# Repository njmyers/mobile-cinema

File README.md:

## Description

Mobile cinema is an audio/visual presentation unit designed for the rough conditions of the field. It is a solar powered, efficient and durable system that can endure the hardships associated with transportation, inclement weather and outdoor conditions. It emphasizes power efficiency and usability over features to create a product that satisfies the use case as cleanly as possible.

The cinema uses a pre-fabricated case with custom electronic and physical parts. Physical parts are fabricated using 3D printing and 2D laser cutting. The materials used are PETG for printing and matte acrylic for 2D cut parts. The parts are then assembled using a combination of structural plastic adhesives and M3 hardware. Electronic parts include some store bought parts such as the TV and solar panel as well as custom circuit boards for routing and switching. All electronics are mounted using printed parts and wiring is done by hand.

The end result is a highly durable, flexible and efficient product that performs very well under harsh conditions and can be easily operated after a simple training session.

## BOM

Parts lists are located in this repository as well as the following [google sheet](https://docs.google.com/spreadsheets/d/1YABbkeHETHl9nhduOOJQ0aeivhLUgdqu8qCclFDEOm0/edit?usp=sharing).

## Photos

_Village Video v4.1 Product Photo_

_Village Video v4.1 Top View_

_Village Video v4.1 In Use_

## Links

- PVI International [Project Description](https://www.pvinternational.org/projects/kibanda-boda/)
- PVI International [v4.0 Release](https://www.pvinternational.org/news/pvi-launches-village-video-4-0/)

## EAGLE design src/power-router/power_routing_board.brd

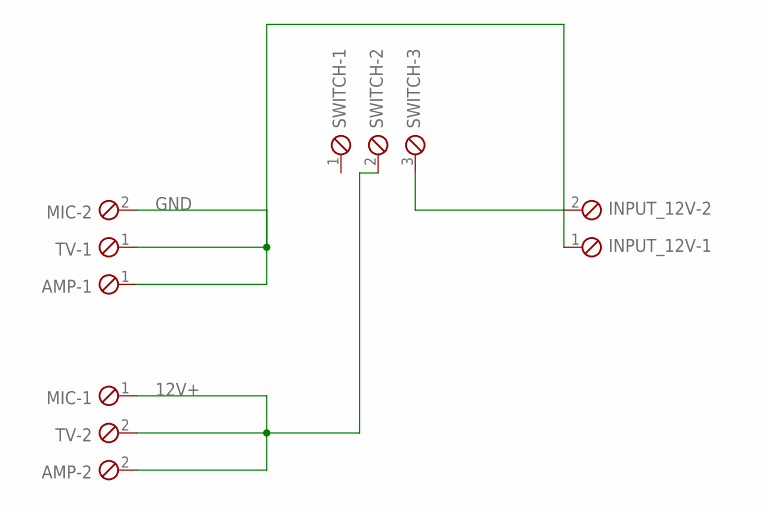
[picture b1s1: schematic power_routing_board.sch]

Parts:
AMP: TB3POL; 2POL381
INPUT_12V: TB3POL; 2POL381
MIC: TB3POL; 2POL381
SWITCH: TB3POL; 3POL381
TV: TB3POL; 2POL381

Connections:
12V+: AMP.2, MIC.1, SWITCH.2, TV.2
GND: AMP.1, INPUT_12V.1, MIC.2, TV.1
unnamed: INPUT_12V.2, SWITCH.3

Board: 2 copper layers, 5 parts (0 on the bottom side), 3 nets, no tracks yet.

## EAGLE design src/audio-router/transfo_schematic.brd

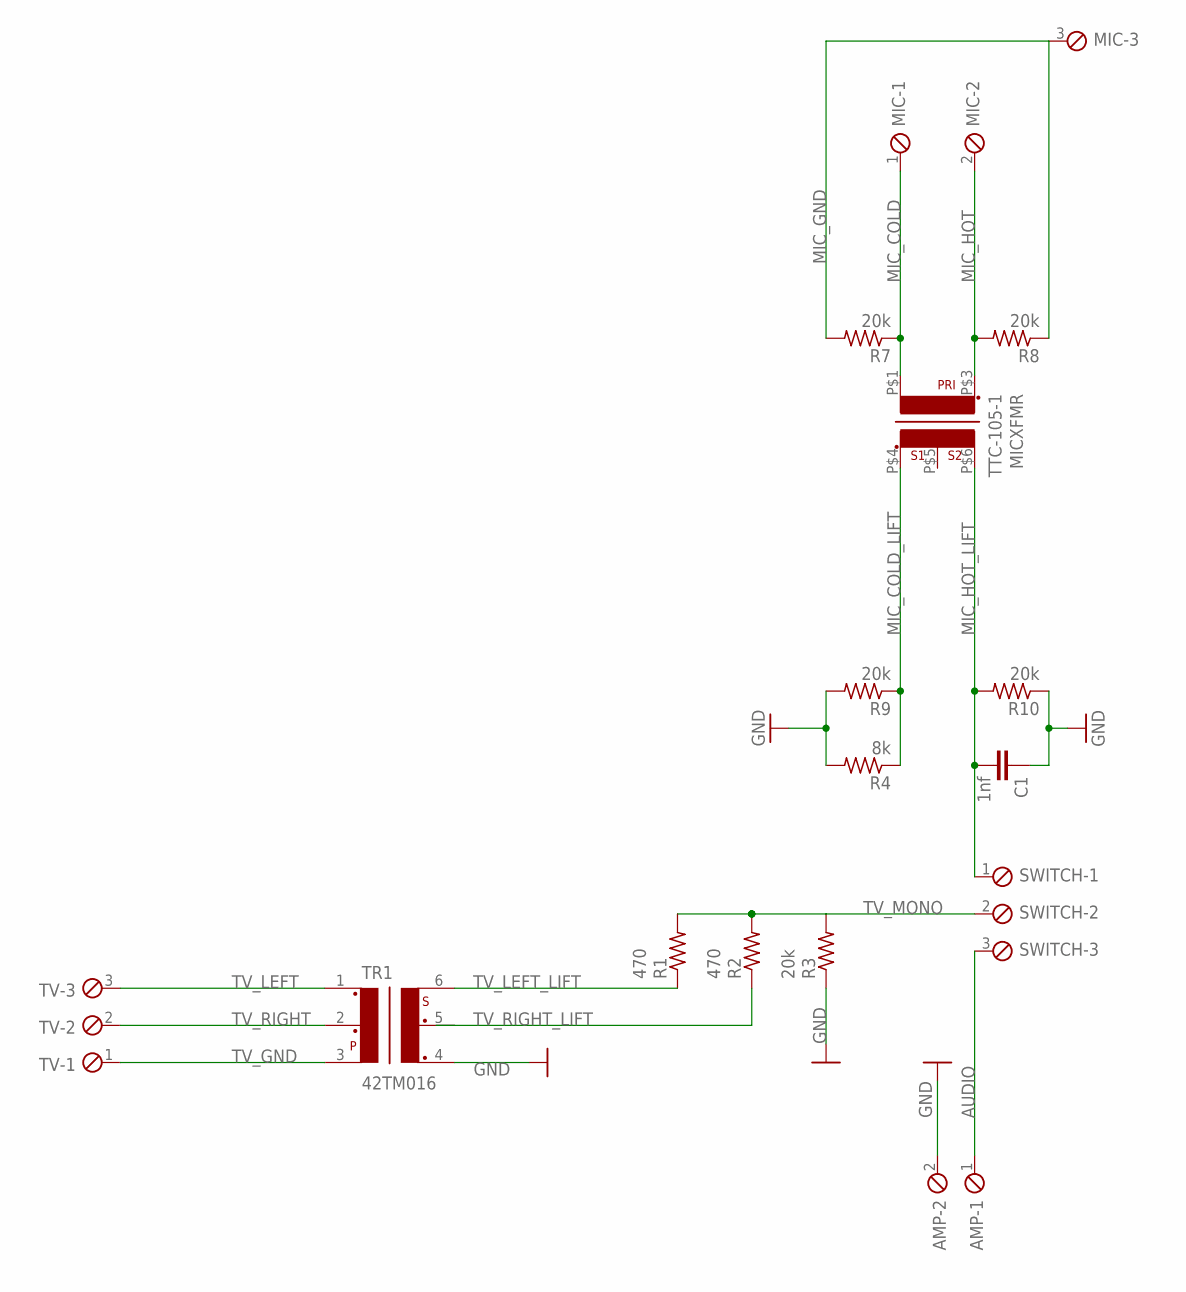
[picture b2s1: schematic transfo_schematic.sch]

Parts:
AMP: TB3POL; 2POL381
C1: 1nf; CAP-PTH-SMALL-KIT
MIC: TB3POL; 3POL381
MICXFMR: TTC-105-1; TAMURA-TTC-105-1
R1, R2: 470; 0204/7
R3, R7, R8, R9, R10: 20k; 0204/7
R4: 8k; 0204/7
SWITCH: TB3POL; 3POL381
TR1: 42TM016; 42TM
TV: TB3POL; 3POL381

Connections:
AUDIO: AMP.1, SWITCH.3
GND: AMP.2, C1.1, R3.1, R4.2, R9.2, R10.1, TR1.4
MIC_COLD: MIC.1, MICXFMR.P$1 (1), R7.1
MIC_COLD_LIFT: MICXFMR.P$4 (4), R4.1, R9.1
MIC_GND: MIC.3, R7.2, R8.1
MIC_HOT: MIC.2, MICXFMR.P$3 (3), R8.2
MIC_HOT_LIFT: C1.2, MICXFMR.P$6 (6), R10.2, SWITCH.1
TV_GND: TR1.3, TV.1
TV_LEFT: TR1.1, TV.3
TV_LEFT_LIFT: R1.1, TR1.6
TV_MONO: R1.2, R2.2, R3.2, SWITCH.2
TV_RIGHT: TR1.2, TV.2
TV_RIGHT_LIFT: R2.1, TR1.5

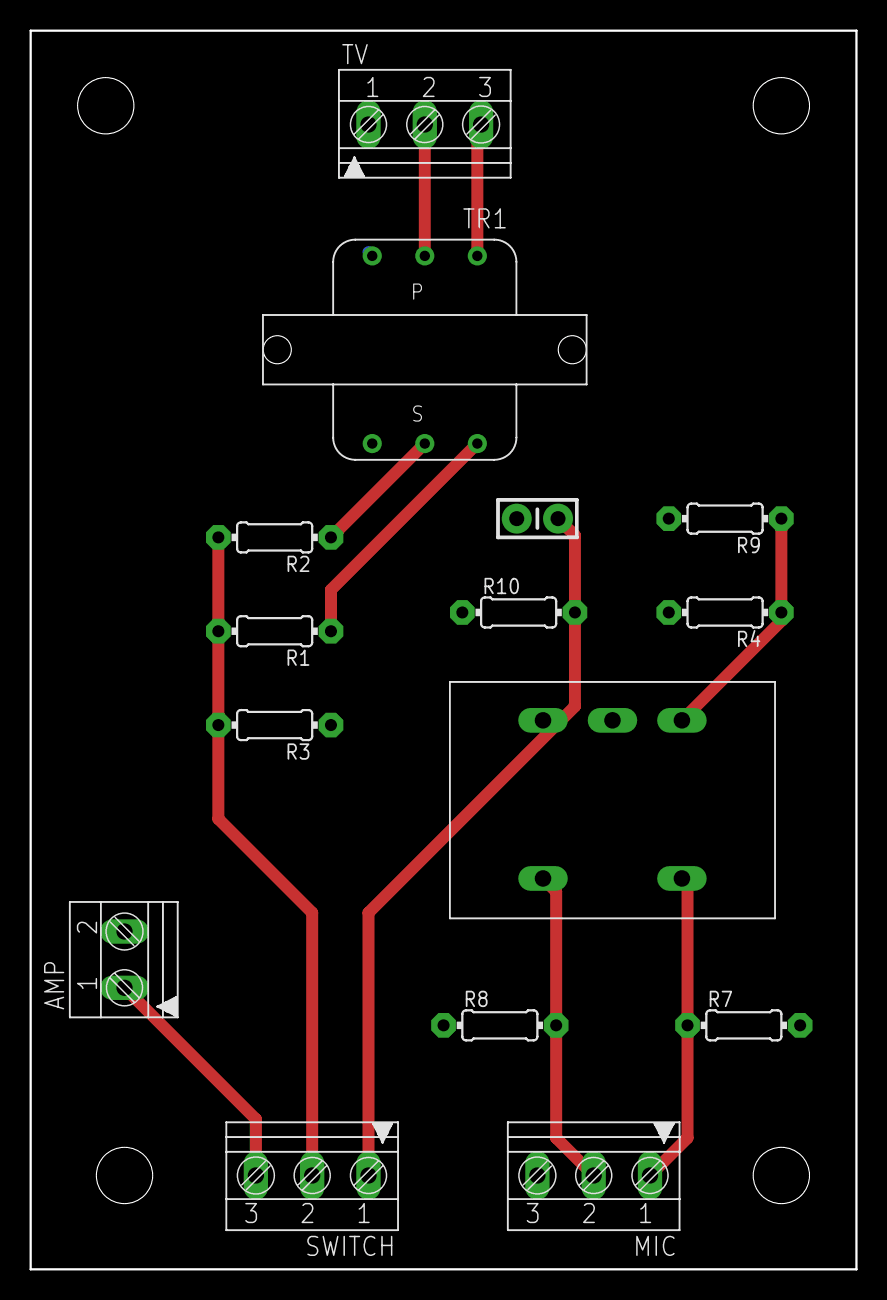
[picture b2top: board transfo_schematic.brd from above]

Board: 2 copper layers, 55.9 x 83.8 mm, 15 parts (0 on the bottom side), 13 nets.

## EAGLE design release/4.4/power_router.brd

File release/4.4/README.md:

### v4.4 Notes

This version has some great improvements. Most notable is the addition of a full depth bracket system for affixing the io panel, a power routing board, and fully transformer isolated audio inputs.

All boards now feature BOMs as well as an updated parts list for other commercially bought parts. Overall time to assemble a unit should be much less following these improvements.

### Changes

- Fixed terminal blocks for all connectors
- Transformer isolated audio inputs
- Full depth brackets for io board mounting
- Power routing board for easier assembly
- BOMs and parts lists
- Addition of TV spacer print file for different TV versions

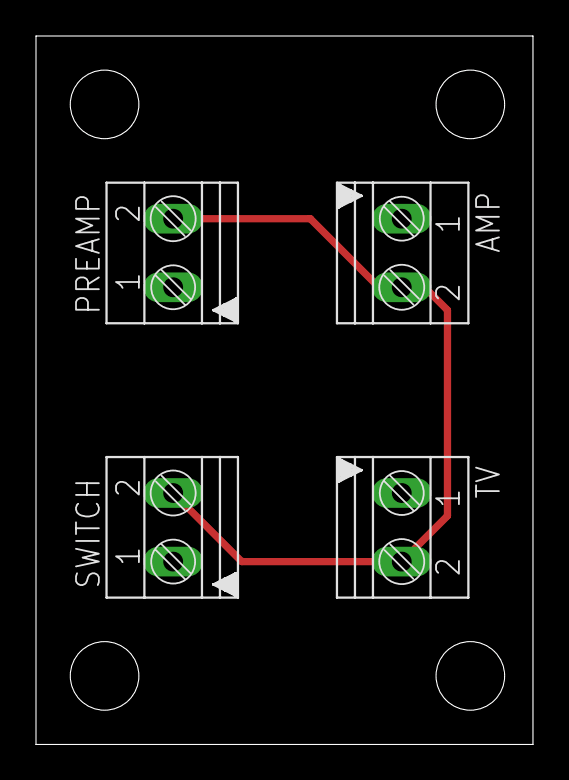
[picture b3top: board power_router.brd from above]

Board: 2 copper layers, 27.6 x 39.4 mm, 4 parts (0 on the bottom side), 2 nets.

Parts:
AMP: MKDS1/2-3,81; 2POL381
PREAMP: MKDS1/2-3,81; 2POL381
SWITCH: MKDS1/2-3,81; 2POL381
TV: MKDS1/2-3,81; 2POL381

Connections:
+12V: AMP.2, PREAMP.2, SWITCH.2, TV.2
GND: AMP.1, PREAMP.1, SWITCH.1, TV.1

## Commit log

2018-11-24 created schematic for audio circuit
2018-12-12 added electrical panel
2018-12-12 added panel brackets
2018-12-17 updated electrical panel files to accomodate usb spacing
2019-01-10 added rhino files for amplifier mounting panels
2019-01-10 WIP readme
2019-01-10 added new export files form amplifier-mount and panel-bracket and new source files for panel-bracket
2019-03-11 Added v4.1 release notes
2019-03-11 Changed directory structure
2019-04-25 Add v4.2 electrical panel
2019-04-25 Rename notes.md -> README.md
2019-04-25 Add artifacts to .gitignore
2019-04-25 Remove top level node scripts
2019-04-25 Copied v4.1 reusable designs to v4.2
2021-06-19 Add parts list
2021-12-11 New router board
2022-05-31 v4.3 board design
2022-05-31 v4.4 board design
2022-05-31 Remove unused files
2022-05-31 Add io-panel directory
2022-05-31 Add 4.3 release files
2022-09-06 Add additional source files
2023-01-30 Include libraries in project
2023-01-30 Create WIP power router board
2023-01-30 Add WIP mic preamp
2023-02-07 Add new power_router board and schematic
2023-02-07 Move files
2023-02-07 Update libs
2023-02-07 Update gitignore
2023-02-07 Rename
2023-02-07 Reorganize
2023-02-17 Add BOMs
2023-02-17 Add link to google sheet
2023-02-17 Update parts data
2023-02-17 Format readme
2023-02-17 Create 4.4 release save point
2023-02-19 Add photos
2023-02-19 Fix links
2023-02-19 Add links
2023-02-19 Change name to village video

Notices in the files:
parts and their libraries:
SparkFun-Capacitors: Licensing: Creative Commons ShareAlike 4.0 International - https://creativecommons.org/licenses/by-sa/4.0
